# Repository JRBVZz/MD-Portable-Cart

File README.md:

#### Картридж для карманной консоли MD Portable

В основе картриджа одна микросхема Flash ROM в корпусе TSOP48 или TSOP56, в зависимости от объема памяти. Для прошивки игры нужен отдельный программатор.

ВНИМАНИЕ, сторона с чипом памяти является обратной стороной по отношению к экрану MD Portable.
Многоигровки на Flash объемом 8МБ и выше не тестировались.

Проект создан в [**KiCad 9**](https://www.kicad.org/).

#### Параметры для изготовления PCB
* 2 слоя
* Толщина PCB: 1.2 мм
* Рекомендуется ENIG покрытие контактов краевого разъема

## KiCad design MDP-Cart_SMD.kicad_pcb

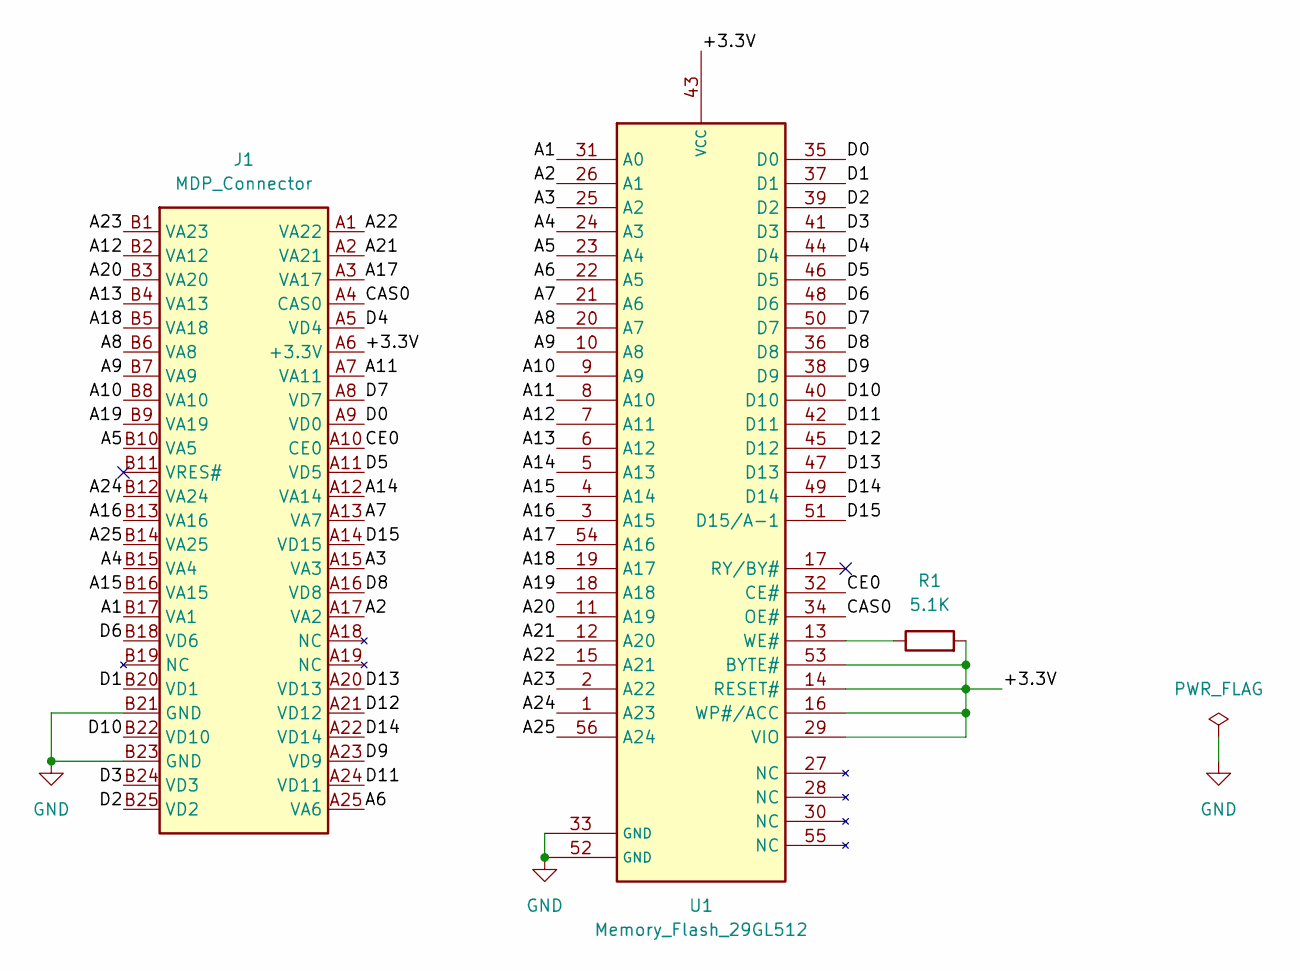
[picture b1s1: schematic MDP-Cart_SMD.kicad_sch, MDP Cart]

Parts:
J1: MDP_Connector
R1: 5.1K; R_0603_1608Metric_Pad0.98x0.95mm_HandSolder
U1: Memory_Flash_29GL512; TSOP-I-56_18.4x14mm_P0.5mm

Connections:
/+3.3V: J1.A6 (+3.3V), R1.2, U1.14 (RESET#), U1.16 (WP#/ACC), U1.29 (VIO), U1.43 (VCC), U1.53 (BYTE#)
/A1: J1.B17 (VA1), U1.31 (A0)
/A2: J1.A17 (VA2), U1.26 (A1)
/A3: J1.A15 (VA3), U1.25 (A2)
/A4: J1.B15 (VA4), U1.24 (A3)
/A5: J1.B10 (VA5), U1.23 (A4)
/A6: J1.A25 (VA6), U1.22 (A5)
/A7: J1.A13 (VA7), U1.21 (A6)
/A8: J1.B6 (VA8), U1.20 (A7)
/A9: J1.B7 (VA9), U1.10 (A8)
/A10: J1.B8 (VA10), U1.9 (A9)
/A11: J1.A7 (VA11), U1.8 (A10)
/A12: J1.B2 (VA12), U1.7 (A11)
/A13: J1.B4 (VA13), U1.6 (A12)
/A14: J1.A12 (VA14), U1.5 (A13)
/A15: J1.B16 (VA15), U1.4 (A14)
/A16: J1.B13 (VA16), U1.3 (A15)
/A17: J1.A3 (VA17), U1.54 (A16)
/A18: J1.B5 (VA18), U1.19 (A17)
/A19: J1.B9 (VA19), U1.18 (A18)
/A20: J1.B3 (VA20), U1.11 (A19)
/A21: J1.A2 (VA21), U1.12 (A20)
/A22: J1.A1 (VA22), U1.15 (A21)
/A23: J1.B1 (VA23), U1.2 (A22)
/A24: J1.B12 (VA24), U1.1 (A23)
/A25: J1.B14 (VA25), U1.56 (A24)
/CAS0: J1.A4 (CAS0), U1.34 (OE#)
/CE0: J1.A10 (CE0), U1.32 (CE#)
/D0: J1.A9 (VD0), U1.35 (D0)
/D1: J1.B20 (VD1), U1.37 (D1)
/D2: J1.B25 (VD2), U1.39 (D2)
/D3: J1.B24 (VD3), U1.41 (D3)
/D4: J1.A5 (VD4), U1.44 (D4)
/D5: J1.A11 (VD5), U1.46 (D5)
/D6: J1.B18 (VD6), U1.48 (D6)
/D7: J1.A8 (VD7), U1.50 (D7)
/D8: J1.A16 (VD8), U1.36 (D8)
/D9: J1.A23 (VD9), U1.38 (D9)
/D10: J1.B22 (VD10), U1.40 (D10)
/D11: J1.A24 (VD11), U1.42 (D11)
/D12: J1.A21 (VD12), U1.45 (D12)
/D13: J1.A20 (VD13), U1.47 (D13)
/D14: J1.A22 (VD14), U1.49 (D14)
/D15: J1.A14 (VD15), U1.51 (D15/A-1)
GND: J1.B21 (GND), J1.B23 (GND), U1.33 (GND), U1.52 (GND)
unnamed: R1.1, U1.13 (WE#)

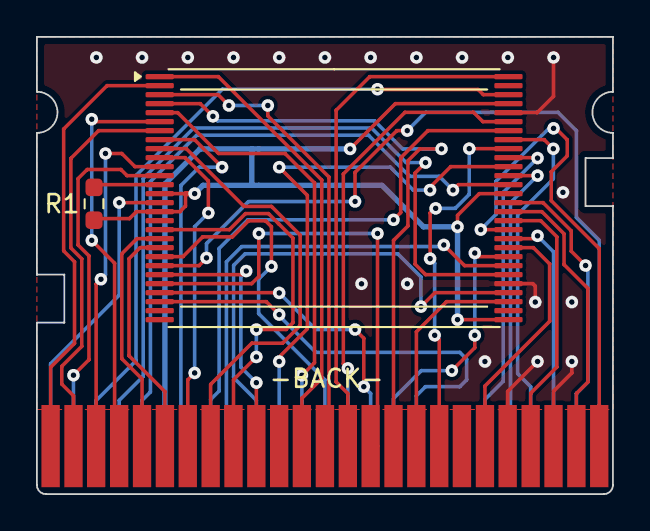
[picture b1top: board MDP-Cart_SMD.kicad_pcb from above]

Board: 2 copper layers, 32.0 x 25.4 mm, 3 parts (0 on the bottom side), 46 nets.
